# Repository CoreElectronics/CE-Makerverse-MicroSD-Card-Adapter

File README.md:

# Makerverse™ MicroSD Card Adapter

This is the repo for the Core Electronics [Makerverse™ MicroSD Card Adapter](https://core-electronics.com.au/catalog/product/view/sku/CE07926).

The PCB project requires KiCAD 5.99 or later to edit but the PDF schematic is in the Documents folder.

## License
This project is open source - please review the LICENSE.md file for further licensing information.

If you have any technical questions, or concerns about licensing, please contact technical support on the [Core Electronics forums](https://forum.core-electronics.com.au/).

*\"Makerverse\" and the Makerverse logo are trademarks of Core Electronics Pty Ltd.*

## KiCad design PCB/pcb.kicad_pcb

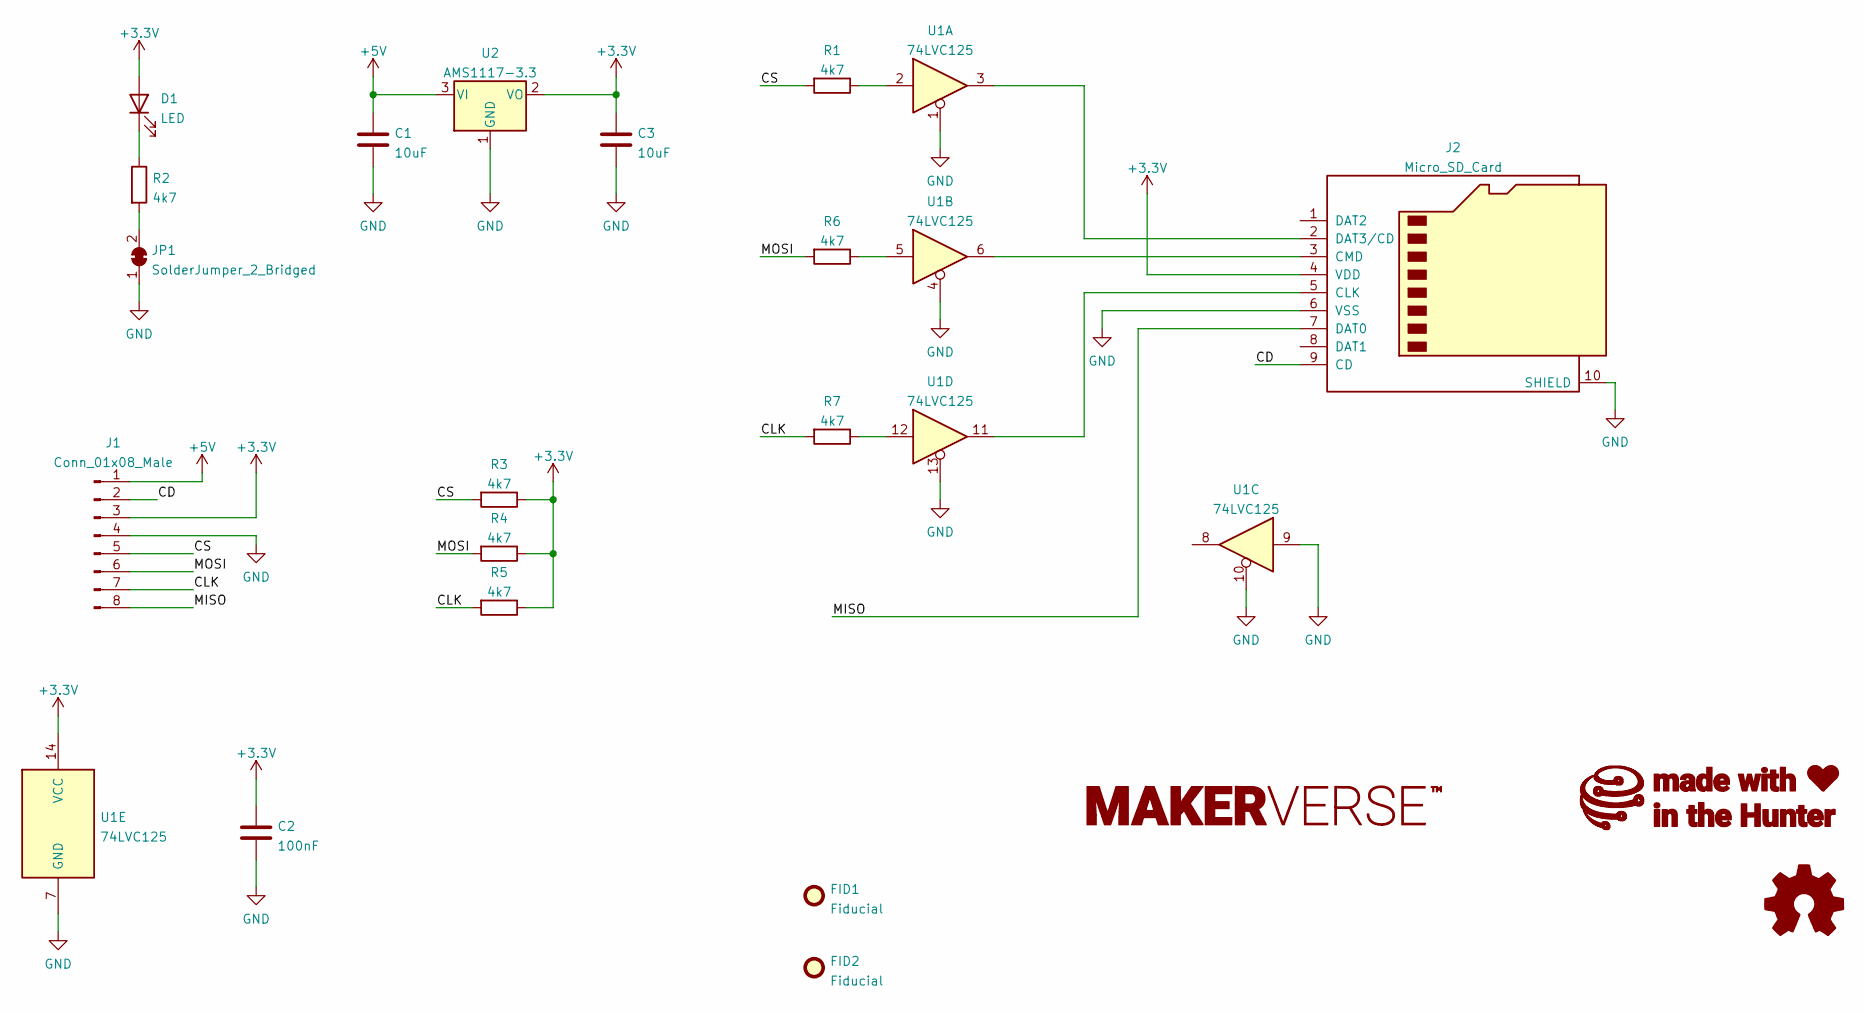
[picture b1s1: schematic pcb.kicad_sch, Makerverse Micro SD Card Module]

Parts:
C1, C3: 10uF; C_0603_1608Metric
C2: 100nF; C_0402_1005Metric
D1: LED; LED_0603_1608Metric
FID1, FID2: Fiducial; Fiducial_1mm_Mask2mm
J1: Conn_01x08_Male; PinHeader_1x08_P2.54mm_Vertical_SMD_Symmetric
J2: Micro_SD_Card; Micro-SD-9Pin
JP1: SolderJumper_2_Bridged; SolderJumper-2_P1.3mm_Bridged_RoundedPad1.0x1.5mm
R1, R2, R3, R4, R5, R6, R7: 4k7; R_0402_1005Metric
U1: 74LVC125; QFN50P250X300X100-15N-D
U2: AMS1117-3.3; SOT-89-3

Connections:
+3V3: C2.1, C3.1, D1.2 (A), J1.3, J2.4 (VDD), R3.1, R4.1, R5.1, U1.14 (VCC), U2.2 (VO)
+5V: C1.1, J1.1, U2.3 (VI)
/CD: J1.2, J2.9 (CD)
/CLK: J1.7, R5.2, R7.2
/CS: J1.5, R1.2, R3.2
/MISO: J1.8, J2.7 (DAT0)
/MOSI: J1.6, R4.2, R6.2
GND: C1.2, C2.2, C3.2, J1.4, J2.6 (VSS), J2.10 (SHIELD), JP1.1 (A), U1.1, U1.4, U1.7 (GND), U1.9, U1.10, U1.13, U2.1 (GND)
unnamed: D1.1 (K), R2.1
unnamed: J2.2 (DAT3/CD), U1.3
unnamed: J2.3 (CMD), U1.6
unnamed: J2.5 (CLK), U1.11
unnamed: JP1.2 (B), R2.2
unnamed: R1.1, U1.2
unnamed: R6.1, U1.5
unnamed: R7.1, U1.12

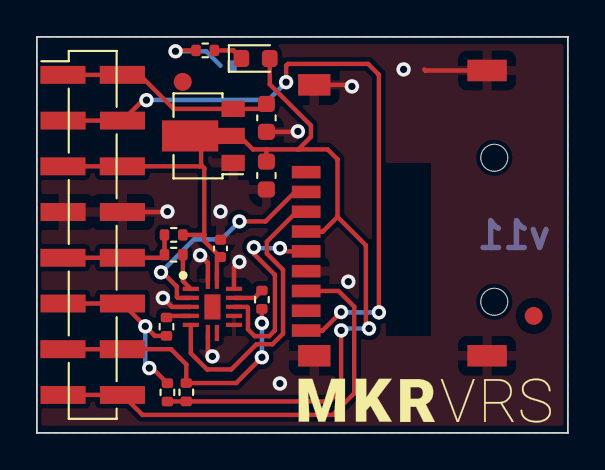
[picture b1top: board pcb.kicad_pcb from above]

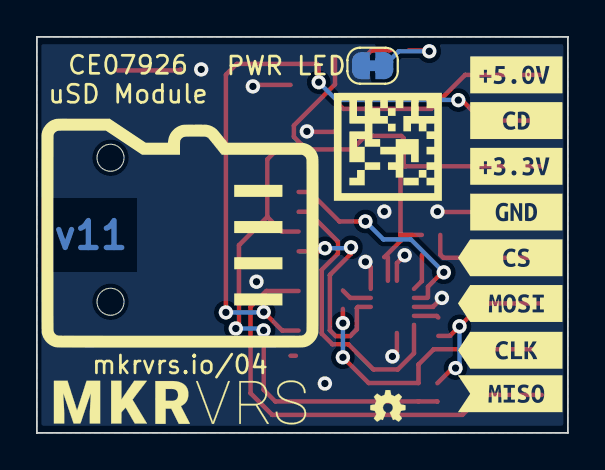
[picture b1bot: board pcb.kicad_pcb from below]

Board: 2 copper layers, 29.5 x 22.0 mm, 26 parts (9 on the bottom side), 16 nets.

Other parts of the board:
kibuzzard-6110B0BA: G***; kibuzzard-6110B0BA
kibuzzard-6110B0C2: G***; kibuzzard-6110B0C2
kibuzzard-6110B0C8: G***; kibuzzard-6110B0C8
kibuzzard-6110B0D8: G***; kibuzzard-6110B0D8
kibuzzard-6110B06E: G***; kibuzzard-6110B06E
kibuzzard-6110B07E: G***; kibuzzard-6110B07E
kibuzzard-6110B094: G***; kibuzzard-6110B094
kibuzzard-6111B463: G***; kibuzzard-6111B463

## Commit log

2021-12-06 Initial commit.
2021-12-06 Removed deprecated code.
2021-12-06 Pre-publish commit

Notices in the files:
PCB/pcb.kicad_pcb:
License: CCASAv4.0 https://creativecommons.org/licenses/by-sa/4.0
